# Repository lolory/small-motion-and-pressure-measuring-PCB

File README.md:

# small-motion-and-pressure-measuring-PCB
A small PCB with a IMU and gyroscope with a separate Pressuresensorboard for connection to a microcontroller with I2C

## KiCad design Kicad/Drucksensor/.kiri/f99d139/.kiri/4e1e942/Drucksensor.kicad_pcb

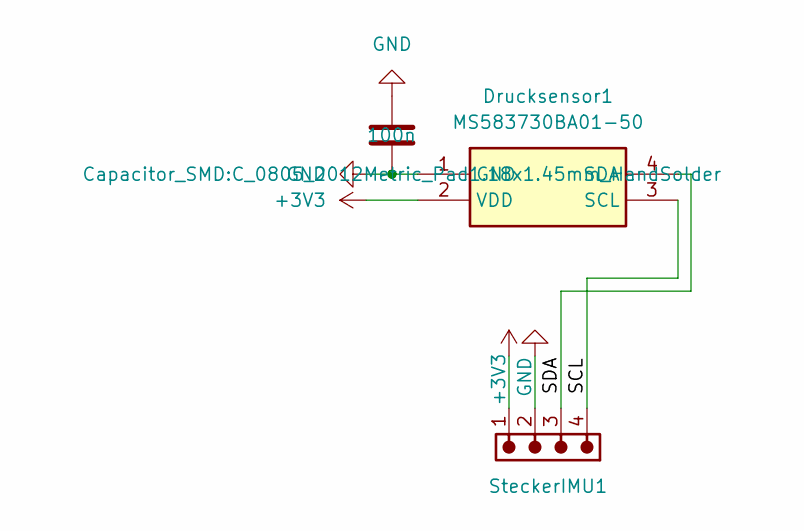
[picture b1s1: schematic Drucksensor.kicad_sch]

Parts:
C4: 100n; C_0805_2012Metric_Pad1.18x1.45mm_HandSolder
Drucksensor1: MS583730BA01-50; MS583730BA0150; Manufacturer_Part_Number MS583730BA01-50; Mouser Part Number 824-MS583730BA01-50
SteckerIMU1: 61900411021; J_Wurth_WR-WTB_61900411021; Working Voltage (V (AC)) 250

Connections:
+3V3: Drucksensor1.2 (VDD), SteckerIMU1.1
/SCL: Drucksensor1.3 (SCL), SteckerIMU1.4
/SDA: Drucksensor1.4 (SDA), SteckerIMU1.3
GND: C4.1, C4.2, Drucksensor1.1 (GND), SteckerIMU1.2

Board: 2 copper layers, 3 parts (0 on the bottom side), 4 nets, no tracks yet.

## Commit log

2025-08-11 gelöscht
    gelöscht
2025-08-11 Test
    Test
2025-08-11 Test2
    Test2
2025-08-12 test
